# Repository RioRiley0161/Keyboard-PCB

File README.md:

# Keyboard-PCB
Custom Keyboard Design

A new project for a custom keyboard design all the way down to the PCB.
We will be making a keyboard with only 41 keys *full sized keyboards are 104 keys
Please feel free to have a look at the files and use them for your own project if need be.
Thanks

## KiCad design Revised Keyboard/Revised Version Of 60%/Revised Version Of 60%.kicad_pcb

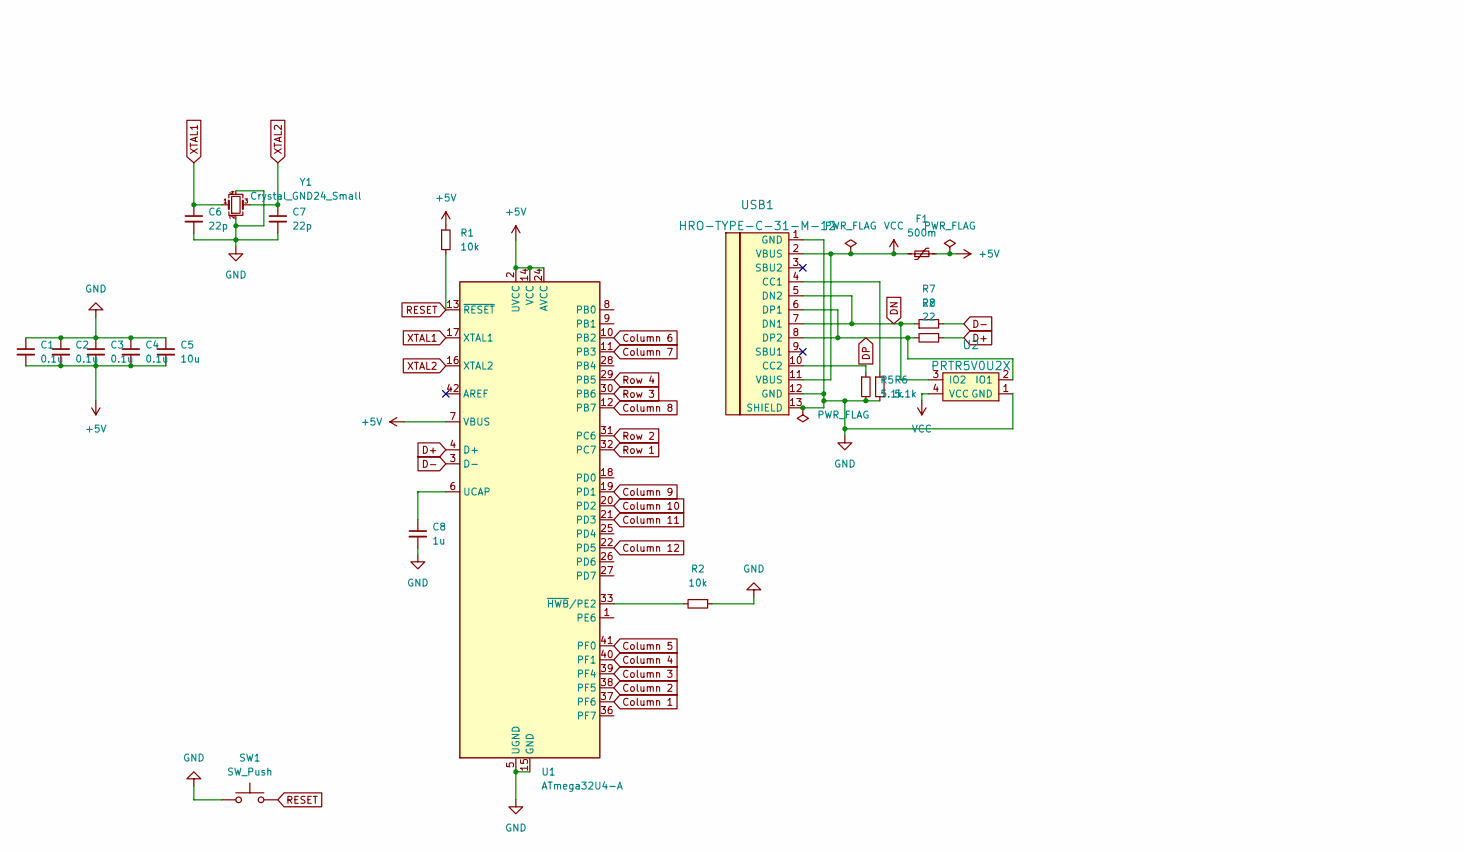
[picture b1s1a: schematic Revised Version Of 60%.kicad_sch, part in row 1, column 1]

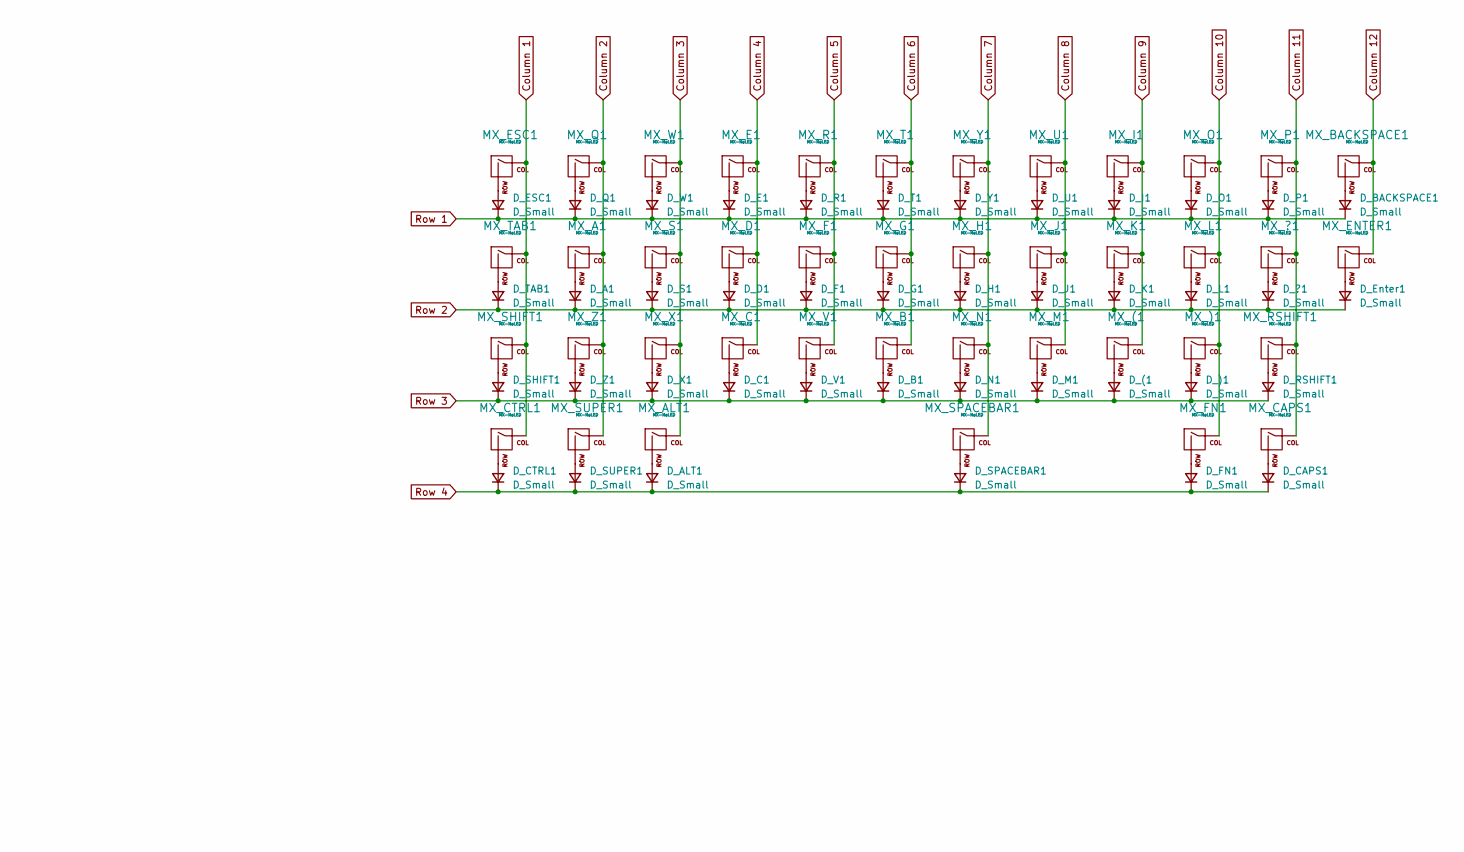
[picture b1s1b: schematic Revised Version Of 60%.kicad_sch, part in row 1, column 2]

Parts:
C1, C2, C3, C4: 0.1u; C_0805_2012Metric_Pad1.18x1.45mm_HandSolder
C5: 10u; C_0805_2012Metric_Pad1.18x1.45mm_HandSolder
C6, C7: 22p; C_0805_2012Metric_Pad1.18x1.45mm_HandSolder
C8: 1u; C_0805_2012Metric
D_(1: D_Small; D_SOD-123
D_)1: D_Small; D_SOD-123
D_?1: D_Small; D_SOD-123
D_A1: D_Small; D_SOD-123
D_ALT1: D_Small; D_SOD-123
D_B1: D_Small; D_SOD-123
D_BACKSPACE1: D_Small; D_SOD-123
D_C1: D_Small; D_SOD-123
D_CAPS1: D_Small; D_SOD-123
D_CTRL1: D_Small; D_SOD-123
D_D1: D_Small; D_SOD-123
D_E1: D_Small; D_SOD-123
D_ESC1: D_Small; D_SOD-123
D_Enter1: D_Small; D_SOD-123
D_F1: D_Small; D_SOD-123
D_FN1: D_Small; D_SOD-123
D_G1: D_Small; D_SOD-123
D_H1: D_Small; D_SOD-123
D_I1: D_Small; D_SOD-123
D_J1: D_Small; D_SOD-123
D_K1: D_Small; D_SOD-123
D_L1: D_Small; D_SOD-123
D_M1: D_Small; D_SOD-123
D_N1: D_Small; D_SOD-123
D_O1: D_Small; D_SOD-123
D_P1: D_Small; D_SOD-123
D_Q1: D_Small; D_SOD-123
D_R1: D_Small; D_SOD-123
D_RSHIFT1: D_Small; D_SOD-123
D_S1: D_Small; D_SOD-123
D_SHIFT1: D_Small; D_SOD-123
D_SPACEBAR1: D_Small; D_SOD-123
D_SUPER1: D_Small; D_SOD-123
D_T1: D_Small; D_SOD-123
D_TAB1: D_Small; D_SOD-123
D_U1: D_Small; D_SOD-123
D_V1: D_Small; D_SOD-123
D_W1: D_Small; D_SOD-123
D_X1: D_Small; D_SOD-123
D_Y1: D_Small; D_SOD-123
D_Z1: D_Small; D_SOD-123
F1: 500m; Fuse_1206_3216Metric_Pad1.42x1.75mm_HandSolder
MX_(1: MX-NoLED; MX-1U-NoLED
MX_)1: MX-NoLED; MX-1U-NoLED
MX_?1: MX-NoLED; MX-1U-NoLED
MX_A1: MX-NoLED; MX-1U-NoLED
MX_ALT1: MX-NoLED; MX-1.25U-NoLED
MX_B1: MX-NoLED; MX-1U-NoLED
MX_BACKSPACE1: MX-NoLED; MX-1.75U-NoLED
MX_C1: MX-NoLED; MX-1U-NoLED
MX_CAPS1: MX-NoLED; MX-1.25U-NoLED
MX_CTRL1: MX-NoLED; MX-1.25U-NoLED
MX_D1: MX-NoLED; MX-1U-NoLED
MX_E1: MX-NoLED; MX-1U-NoLED
MX_ENTER1: MX-NoLED; MX-1.5U-NoLED
MX_ESC1: MX-NoLED; MX-1U-NoLED
MX_F1: MX-NoLED; MX-1U-NoLED
MX_FN1: MX-NoLED; MX-1.25U-NoLED
MX_G1: MX-NoLED; MX-1U-NoLED
MX_H1: MX-NoLED; MX-1U-NoLED
MX_I1: MX-NoLED; MX-1U-NoLED
MX_J1: MX-NoLED; MX-1U-NoLED
MX_K1: MX-NoLED; MX-1U-NoLED
MX_L1: MX-NoLED; MX-1U-NoLED
MX_M1: MX-NoLED; MX-1U-NoLED
MX_N1: MX-NoLED; MX-1U-NoLED
MX_O1: MX-NoLED; MX-1U-NoLED
MX_P1: MX-NoLED; MX-1U-NoLED
MX_Q1: MX-NoLED; MX-1U-NoLED
MX_R1: MX-NoLED; MX-1U-NoLED
MX_RSHIFT1: MX-NoLED; MX-2U-NoLED
MX_S1: MX-NoLED; MX-1U-NoLED
MX_SHIFT1: MX-NoLED; MX-1.75U-NoLED
MX_SPACEBAR1: MX-NoLED; MX-6.5U-NoLED
MX_SUPER1: MX-NoLED; MX-1.25U-NoLED
MX_T1: MX-NoLED; MX-1U-NoLED
MX_TAB1: MX-NoLED; MX-1.25U-NoLED
MX_U1: MX-NoLED; MX-1U-NoLED
MX_V1: MX-NoLED; MX-1U-NoLED
MX_W1: MX-NoLED; MX-1U-NoLED
MX_X1: MX-NoLED; MX-1U-NoLED
MX_Y1: MX-NoLED; MX-1U-NoLED
MX_Z1: MX-NoLED; MX-1U-NoLED
R1, R2: 10k; R_0805_2012Metric_Pad1.20x1.40mm_HandSolder
R5, R6: 5.1k; R_0805_2012Metric_Pad1.20x1.40mm_HandSolder
R7, R8: 22; R_0805_2012Metric_Pad1.20x1.40mm_HandSolder
SW1: SW_Push; SKQG-1155865
U1: ATmega32U4-A; TQFP-44_10x10mm_P0.8mm
U2: PRTR5V0U2X; SOT143B
USB1: HRO-TYPE-C-31-M-12; HRO-TYPE-C-31-M-12-HandSoldering
Y1: Crystal_GND24_Small; Crystal_SMD_3225-4Pin_3.2x2.5mm_HandSoldering

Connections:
+5V: C1.2, C2.2, C3.2, C4.2, C5.2, F1.2, R1.1, U1.2 (UVCC), U1.7 (VBUS), U1.14 (VCC), U1.24 (AVCC), U1.34 (VCC), U1.44 (AVCC)
Column 1: MX_CTRL1.1 (COL), MX_ESC1.1 (COL), MX_SHIFT1.1 (COL), MX_TAB1.1 (COL), U1.37 (PF6)
Column 2: MX_A1.1 (COL), MX_Q1.1 (COL), MX_SUPER1.1 (COL), MX_Z1.1 (COL), U1.38 (PF5)
Column 3: MX_ALT1.1 (COL), MX_S1.1 (COL), MX_W1.1 (COL), MX_X1.1 (COL), U1.39 (PF4)
Column 4: MX_C1.1 (COL), MX_D1.1 (COL), MX_E1.1 (COL), U1.40 (PF1)
Column 5: MX_F1.1 (COL), MX_R1.1 (COL), MX_V1.1 (COL), U1.41 (PF0)
Column 6: MX_B1.1 (COL), MX_G1.1 (COL), MX_T1.1 (COL), U1.10 (PB2)
Column 7: MX_H1.1 (COL), MX_N1.1 (COL), MX_SPACEBAR1.1 (COL), MX_Y1.1 (COL), U1.11 (PB3)
Column 8: MX_J1.1 (COL), MX_M1.1 (COL), MX_U1.1 (COL), U1.12 (PB7)
Column 9: MX_(1.1 (COL), MX_I1.1 (COL), MX_K1.1 (COL), U1.19 (PD1)
Column 10: MX_)1.1 (COL), MX_FN1.1 (COL), MX_L1.1 (COL), MX_O1.1 (COL), U1.20 (PD2)
Column 11: MX_?1.1 (COL), MX_CAPS1.1 (COL), MX_P1.1 (COL), MX_RSHIFT1.1 (COL), U1.21 (PD3)
Column 12: MX_BACKSPACE1.1 (COL), MX_ENTER1.1 (COL), U1.22 (PD5)
D+: R8.1, U1.4 (D+)
D-: R7.2, U1.3 (D-)
DN: R7.1, U2.3 (IO2), USB1.5 (DN2), USB1.7 (DN1)
DP: R8.2, U2.2 (IO1), USB1.6 (DP1), USB1.8 (DP2)
GND: C1.1, C2.1, C3.1, C4.1, C5.1, C6.2, C7.2, C8.2, R2.1, R5.2, R6.2, SW1.1, U1.5 (UGND), U1.15 (GND), U1.23 (GND), U1.35 (GND), U1.43 (GND), U2.1 (GND), USB1.1 (GND), USB1.12 (GND), USB1.13 (SHIELD), Y1.2, Y1.4
unnamed: C8.1, U1.6 (UCAP)
unnamed: D_(1.2 (A), MX_(1.2 (ROW)
unnamed: D_)1.2 (A), MX_)1.2 (ROW)
unnamed: D_?1.2 (A), MX_?1.2 (ROW)
unnamed: D_A1.2 (A), MX_A1.2 (ROW)
unnamed: D_ALT1.2 (A), MX_ALT1.2 (ROW)
unnamed: D_B1.2 (A), MX_B1.2 (ROW)
unnamed: D_BACKSPACE1.2 (A), MX_BACKSPACE1.2 (ROW)
unnamed: D_C1.2 (A), MX_C1.2 (ROW)
unnamed: D_CAPS1.2 (A), MX_CAPS1.2 (ROW)
unnamed: D_CTRL1.2 (A), MX_CTRL1.2 (ROW)
unnamed: D_D1.2 (A), MX_D1.2 (ROW)
unnamed: D_E1.2 (A), MX_E1.2 (ROW)
unnamed: D_ESC1.2 (A), MX_ESC1.2 (ROW)
unnamed: D_Enter1.2 (A), MX_ENTER1.2 (ROW)
unnamed: D_F1.2 (A), MX_F1.2 (ROW)
unnamed: D_FN1.2 (A), MX_FN1.2 (ROW)
unnamed: D_G1.2 (A), MX_G1.2 (ROW)
unnamed: D_H1.2 (A), MX_H1.2 (ROW)
unnamed: D_I1.2 (A), MX_I1.2 (ROW)
unnamed: D_J1.2 (A), MX_J1.2 (ROW)
unnamed: D_K1.2 (A), MX_K1.2 (ROW)
unnamed: D_L1.2 (A), MX_L1.2 (ROW)
unnamed: D_M1.2 (A), MX_M1.2 (ROW)
unnamed: D_N1.2 (A), MX_N1.2 (ROW)
unnamed: D_O1.2 (A), MX_O1.2 (ROW)
unnamed: D_P1.2 (A), MX_P1.2 (ROW)
unnamed: D_Q1.2 (A), MX_Q1.2 (ROW)
unnamed: D_R1.2 (A), MX_R1.2 (ROW)
unnamed: D_RSHIFT1.2 (A), MX_RSHIFT1.2 (ROW)
unnamed: D_S1.2 (A), MX_S1.2 (ROW)
unnamed: D_SHIFT1.2 (A), MX_SHIFT1.2 (ROW)
unnamed: D_SPACEBAR1.2 (A), MX_SPACEBAR1.2 (ROW)
unnamed: D_SUPER1.2 (A), MX_SUPER1.2 (ROW)
unnamed: D_T1.2 (A), MX_T1.2 (ROW)
unnamed: D_TAB1.2 (A), MX_TAB1.2 (ROW)
unnamed: D_U1.2 (A), MX_U1.2 (ROW)
unnamed: D_V1.2 (A), MX_V1.2 (ROW)
unnamed: D_W1.2 (A), MX_W1.2 (ROW)
unnamed: D_X1.2 (A), MX_X1.2 (ROW)
unnamed: D_Y1.2 (A), MX_Y1.2 (ROW)
unnamed: D_Z1.2 (A), MX_Z1.2 (ROW)
unnamed: R2.2, U1.33 (~HWB/PE2)
unnamed: R5.1, USB1.10 (CC2)
unnamed: R6.1, USB1.4 (CC1)
RESET: R1.2, SW1.2, U1.13 (~RESET)
Row 1: D_BACKSPACE1.1 (K), D_E1.1 (K), D_ESC1.1 (K), D_I1.1 (K), D_O1.1 (K), D_P1.1 (K), D_Q1.1 (K), D_R1.1 (K), D_T1.1 (K), D_U1.1 (K), D_W1.1 (K), D_Y1.1 (K), U1.32 (PC7)
Row 2: D_?1.1 (K), D_A1.1 (K), D_D1.1 (K), D_Enter1.1 (K), D_F1.1 (K), D_G1.1 (K), D_H1.1 (K), D_J1.1 (K), D_K1.1 (K), D_L1.1 (K), D_S1.1 (K), D_TAB1.1 (K), U1.31 (PC6)
Row 3: D_(1.1 (K), D_)1.1 (K), D_B1.1 (K), D_C1.1 (K), D_M1.1 (K), D_N1.1 (K), D_RSHIFT1.1 (K), D_SHIFT1.1 (K), D_V1.1 (K), D_X1.1 (K), D_Z1.1 (K), U1.30 (PB6)
Row 4: D_ALT1.1 (K), D_CAPS1.1 (K), D_CTRL1.1 (K), D_FN1.1 (K), D_SPACEBAR1.1 (K), D_SUPER1.1 (K), U1.29 (PB5)
VCC: F1.1, U2.4 (VCC), USB1.2 (VBUS), USB1.11 (VBUS)
XTAL1: C6.1, U1.17 (XTAL1), Y1.1
XTAL2: C7.1, U1.16 (XTAL2), Y1.3

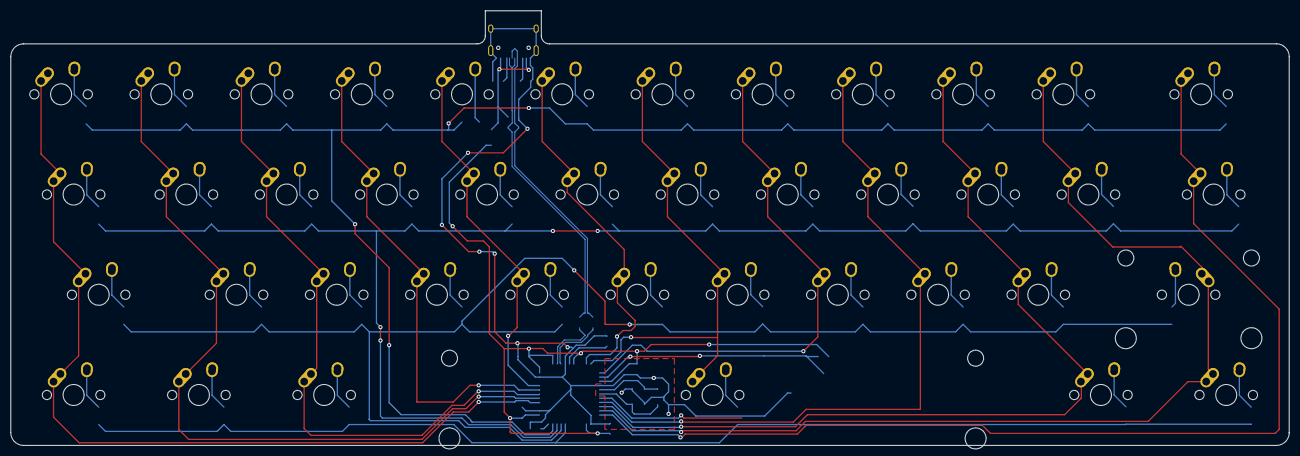
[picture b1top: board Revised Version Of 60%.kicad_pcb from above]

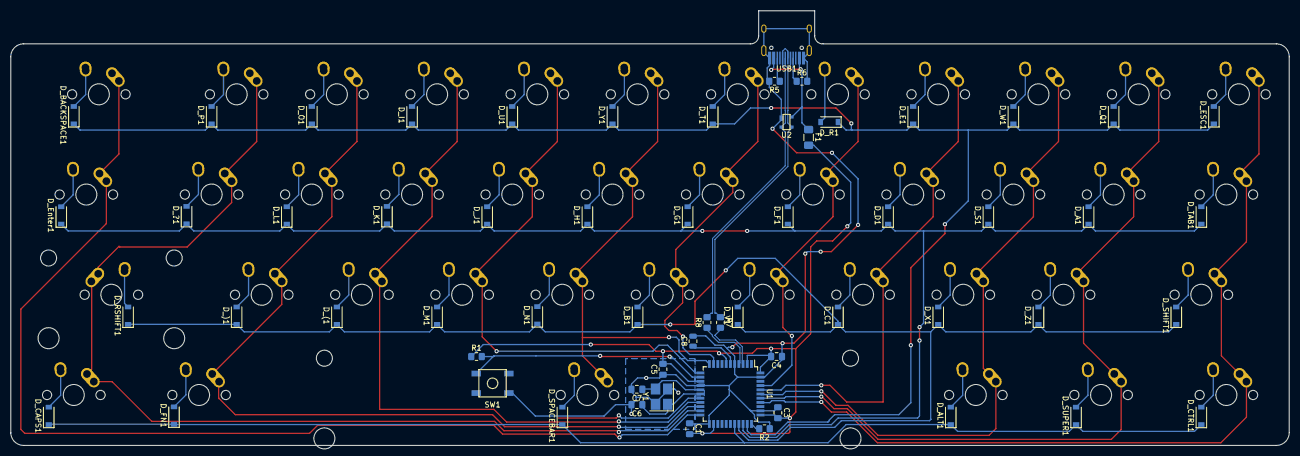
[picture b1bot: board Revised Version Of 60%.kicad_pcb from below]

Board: 2 copper layers, 243.0 x 82.6 mm, 101 parts (61 on the bottom side), 71 nets.

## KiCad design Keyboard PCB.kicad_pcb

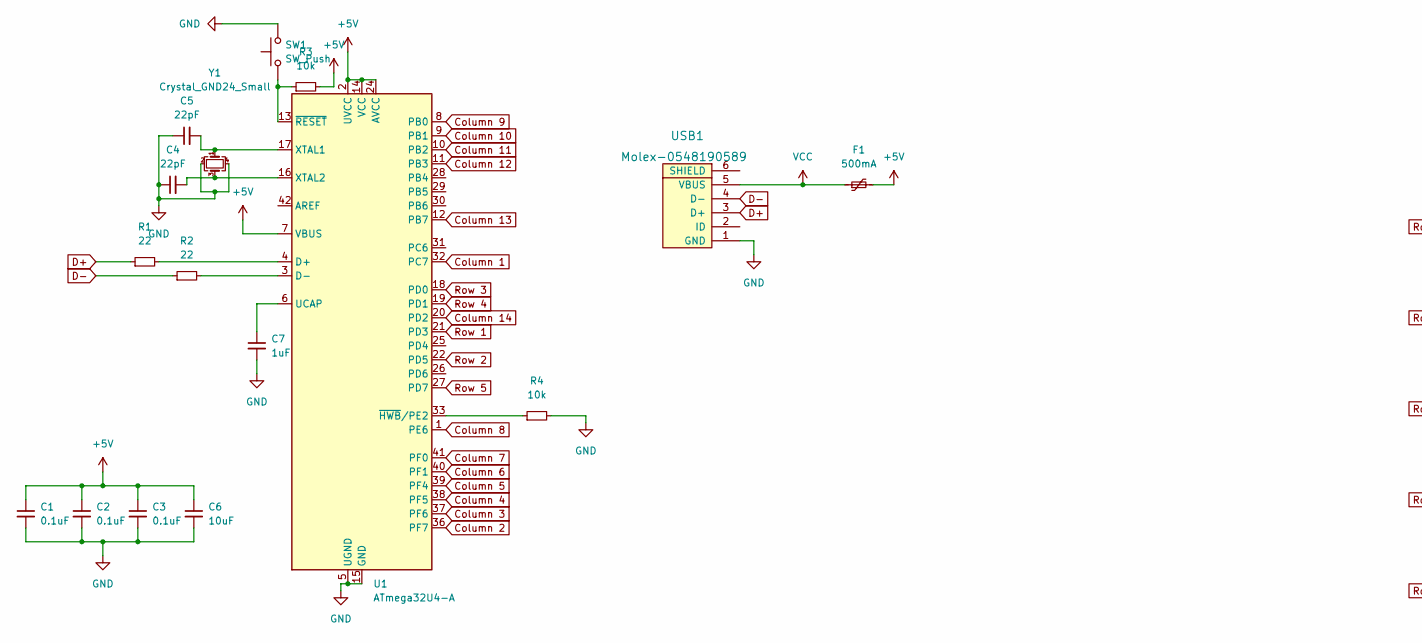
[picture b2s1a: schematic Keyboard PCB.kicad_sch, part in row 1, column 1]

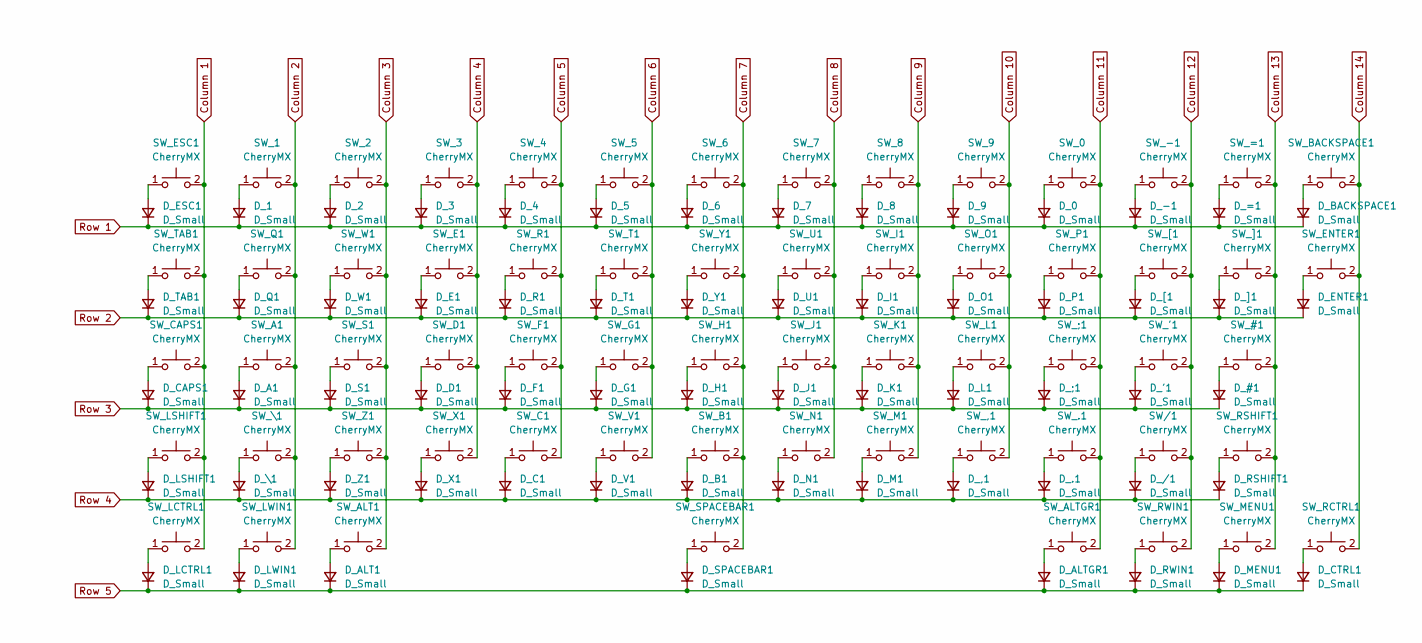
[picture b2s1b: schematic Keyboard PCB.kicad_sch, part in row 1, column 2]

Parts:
C1, C2, C3: 0.1uF; C_0805_2012Metric
C4, C5: 22pF; C_0805_2012Metric
C6: 10uF; C_0805_2012Metric
C7: 1uF; C_0805_2012Metric
D_0, D_1, D_2, D_3, D_4, D_5, D_6, D_7, D_8, D_9, D_.1: D_Small; D_SOD-123
D_#1: D_Small; D_SOD-123
D_'1: D_Small; D_SOD-123
D_,1: D_Small; D_SOD-123
D_-1: D_Small; D_SOD-123
D_/1: D_Small; D_SOD-123
D_;1: D_Small; D_SOD-123
D_=1: D_Small; D_SOD-123
D_A1: D_Small; D_SOD-123
D_ALT1: D_Small; D_SOD-123
D_ALTGR1: D_Small; D_SOD-123
D_B1: D_Small; D_SOD-123
D_BACKSPACE1: D_Small; D_SOD-123
D_C1: D_Small; D_SOD-123
D_CAPS1: D_Small; D_SOD-123
D_CTRL1: D_Small; D_SOD-123
D_D1: D_Small; D_SOD-123
D_E1: D_Small; D_SOD-123
D_ENTER1: D_Small; D_SOD-123
D_ESC1: D_Small; D_SOD-123
D_F1: D_Small; D_SOD-123
D_G1: D_Small; D_SOD-123
D_H1: D_Small; D_SOD-123
D_I1: D_Small; D_SOD-123
D_J1: D_Small; D_SOD-123
D_K1: D_Small; D_SOD-123
D_L1: D_Small; D_SOD-123
D_LCTRL1: D_Small; D_SOD-123
D_LSHIFT1: D_Small; D_SOD-123
D_LWIN1: D_Small; D_SOD-123
D_M1: D_Small; D_SOD-123
D_MENU1: D_Small; D_SOD-123
D_N1: D_Small; D_SOD-123
D_O1: D_Small; D_SOD-123
D_P1: D_Small; D_SOD-123
D_Q1: D_Small; D_SOD-123
D_R1: D_Small; D_SOD-123
D_RSHIFT1: D_Small; D_SOD-123
D_RWIN1: D_Small; D_SOD-123
D_S1: D_Small; D_SOD-123
D_SPACEBAR1: D_Small; D_SOD-123
D_T1: D_Small; D_SOD-123
D_TAB1: D_Small; D_SOD-123
D_U1: D_Small; D_SOD-123
D_V1: D_Small; D_SOD-123
D_W1: D_Small; D_SOD-123
D_X1: D_Small; D_SOD-123
D_Y1: D_Small; D_SOD-123
D_Z1: D_Small; D_SOD-123
D_[1: D_Small; D_SOD-123
D_\1: D_Small; D_SOD-123
D_]1: D_Small; D_SOD-123
F1: 500mA; Fuse_1206_3216Metric
R1, R2: 22; R_0805_2012Metric
R3, R4: 10k; R_0805_2012Metric
SW1: SW_Push; SKQG-1155865
SW/1: CherryMX; MXOnly-1U-NoLED
SW_0, SW_1, SW_2, SW_3, SW_4, SW_5, SW_6, SW_7, SW_8, SW_9, SW_.1: CherryMX; MXOnly-1U-NoLED
SW_#1: CherryMX; MXOnly-1U-NoLED
SW_'1: CherryMX; MXOnly-1U-NoLED
SW_,1: CherryMX; MXOnly-1U-NoLED
SW_-1: CherryMX; MXOnly-1U-NoLED
SW_;1: CherryMX; MXOnly-1U-NoLED
SW_=1: CherryMX; MXOnly-1U-NoLED
SW_A1: CherryMX; MXOnly-1U-NoLED
SW_ALT1: CherryMX; MXOnly-1.25U-NoLED
SW_ALTGR1: CherryMX; MXOnly-1.25U-NoLED
SW_B1: CherryMX; MXOnly-1U-NoLED
SW_BACKSPACE1: CherryMX; MXOnly-2U-NoLED
SW_C1: CherryMX; MXOnly-1U-NoLED
SW_CAPS1: CherryMX; MXOnly-1.75U-NoLED
SW_D1: CherryMX; MXOnly-1U-NoLED
SW_E1: CherryMX; MXOnly-1U-NoLED
SW_ENTER1: CherryMX; MXOnly-ISO
SW_ESC1: CherryMX; MXOnly-1U-NoLED
SW_F1: CherryMX; MXOnly-1U-NoLED
SW_G1: CherryMX; MXOnly-1U-NoLED
SW_H1: CherryMX; MXOnly-1U-NoLED
SW_I1: CherryMX; MXOnly-1U-NoLED
SW_J1: CherryMX; MXOnly-1U-NoLED
SW_K1: CherryMX; MXOnly-1U-NoLED
SW_L1: CherryMX; MXOnly-1U-NoLED
SW_LCTRL1: CherryMX; MXOnly-1.25U-NoLED
SW_LSHIFT1: CherryMX; MXOnly-1.25U-NoLED
SW_LWIN1: CherryMX; MXOnly-1.25U-NoLED
SW_M1: CherryMX; MXOnly-1U-NoLED
SW_MENU1: CherryMX; MXOnly-1.25U-NoLED
SW_N1: CherryMX; MXOnly-1U-NoLED
SW_O1: CherryMX; MXOnly-1U-NoLED
SW_P1: CherryMX; MXOnly-1U-NoLED
SW_Q1: CherryMX; MXOnly-1U-NoLED
SW_R1: CherryMX; MXOnly-1U-NoLED
SW_RCTRL1: CherryMX; MXOnly-1.25U-NoLED
SW_RSHIFT1: CherryMX; MXOnly-2.75U-NoLED
SW_RWIN1: CherryMX; MXOnly-1.25U-NoLED
SW_S1: CherryMX; MXOnly-1U-NoLED
SW_SPACEBAR1: CherryMX; MXOnly-6.25U-NoLED
SW_T1: CherryMX; MXOnly-1U-NoLED
SW_TAB1: CherryMX; MXOnly-1.5U-NoLED
SW_U1: CherryMX; MXOnly-1U-NoLED
SW_V1: CherryMX; MXOnly-1U-NoLED
SW_W1: CherryMX; MXOnly-1U-NoLED
SW_X1: CherryMX; MXOnly-1U-NoLED
SW_Y1: CherryMX; MXOnly-1U-NoLED
SW_Z1: CherryMX; MXOnly-1U-NoLED
SW_[1: CherryMX; MXOnly-1U-NoLED
SW_\1: CherryMX; MXOnly-1U-NoLED
SW_]1: CherryMX; MXOnly-1U-NoLED
U1: ATmega32U4-A; TQFP-44_10x10mm_P0.8mm
USB1: Molex-0548190589
Y1: Crystal_GND24_Small; Crystal_SMD_3225-4Pin_3.2x2.5mm_HandSoldering

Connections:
+5V: C1.1, C2.1, C3.1, C6.1, F1.2, R3.2, U1.2 (UVCC), U1.7 (VBUS), U1.14 (VCC), U1.24 (AVCC), U1.34 (VCC), U1.44 (AVCC)
Column 1: SW_CAPS1.2, SW_ESC1.2, SW_LCTRL1.2, SW_LSHIFT1.2, SW_TAB1.2, U1.32 (PC7)
Column 2: SW_1.2, SW_A1.2, SW_LWIN1.2, SW_Q1.2, SW_\1.2, U1.36 (PF7)
Column 3: SW_2.2, SW_ALT1.2, SW_S1.2, SW_W1.2, SW_Z1.2, U1.37 (PF6)
Column 4: SW_3.2, SW_D1.2, SW_E1.2, SW_X1.2, U1.38 (PF5)
Column 5: SW_4.2, SW_C1.2, SW_F1.2, SW_R1.2, U1.39 (PF4)
Column 6: SW_5.2, SW_G1.2, SW_T1.2, SW_V1.2, U1.40 (PF1)
Column 7: SW_6.2, SW_B1.2, SW_H1.2, SW_SPACEBAR1.2, SW_Y1.2, U1.41 (PF0)
Column 8: SW_7.2, SW_J1.2, SW_N1.2, SW_U1.2, U1.1 (PE6)
Column 9: SW_8.2, SW_I1.2, SW_K1.2, SW_M1.2, U1.8 (PB0)
Column 10: SW_9.2, SW_,1.2, SW_L1.2, SW_O1.2, U1.9 (PB1)
Column 11: SW_0.2, SW_.1.2, SW_;1.2, SW_ALTGR1.2, SW_P1.2, U1.10 (PB2)
Column 12: SW/1.2, SW_'1.2, SW_-1.2, SW_RWIN1.2, SW_[1.2, U1.11 (PB3)
Column 13: SW_#1.2, SW_=1.2, SW_MENU1.2, SW_RSHIFT1.2, SW_]1.2, U1.12 (PB7)
Column 14: SW_BACKSPACE1.2, SW_ENTER1.2, SW_RCTRL1.2, U1.20 (PD2)
D+: R1.1, USB1.3 (D+)
D-: R2.1, USB1.4 (D-)
GND: C1.2, C2.2, C3.2, C4.1, C5.1, C6.2, C7.2, R4.2, SW1.2, U1.5 (UGND), U1.15 (GND), U1.23 (GND), U1.35 (GND), U1.43 (GND), USB1.1 (GND), Y1.2, Y1.4
unnamed: C4.2, U1.16 (XTAL2), Y1.3
unnamed: C5.2, U1.17 (XTAL1), Y1.1
unnamed: C7.1, U1.6 (UCAP)
unnamed: D_0.2 (A), SW_0.1
unnamed: D_1.2 (A), SW_1.1
unnamed: D_2.2 (A), SW_2.1
unnamed: D_3.2 (A), SW_3.1
unnamed: D_4.2 (A), SW_4.1
unnamed: D_5.2 (A), SW_5.1
unnamed: D_6.2 (A), SW_6.1
unnamed: D_7.2 (A), SW_7.1
unnamed: D_8.2 (A), SW_8.1
unnamed: D_9.2 (A), SW_9.1
unnamed: D_#1.2 (A), SW_#1.1
unnamed: D_'1.2 (A), SW_'1.1
unnamed: D_,1.2 (A), SW_,1.1
unnamed: D_-1.2 (A), SW_-1.1
unnamed: D_.1.2 (A), SW_.1.1
unnamed: D_/1.2 (A), SW/1.1
unnamed: D_;1.2 (A), SW_;1.1
unnamed: D_=1.2 (A), SW_=1.1
unnamed: D_A1.2 (A), SW_A1.1
unnamed: D_ALT1.2 (A), SW_ALT1.1
unnamed: D_ALTGR1.2 (A), SW_ALTGR1.1
unnamed: D_B1.2 (A), SW_B1.1
unnamed: D_BACKSPACE1.2 (A), SW_BACKSPACE1.1
unnamed: D_C1.2 (A), SW_C1.1
unnamed: D_CAPS1.2 (A), SW_CAPS1.1
unnamed: D_CTRL1.2 (A), SW_RCTRL1.1
unnamed: D_D1.2 (A), SW_D1.1
unnamed: D_E1.2 (A), SW_E1.1
unnamed: D_ENTER1.2 (A), SW_ENTER1.1
unnamed: D_ESC1.2 (A), SW_ESC1.1
unnamed: D_F1.2 (A), SW_F1.1
unnamed: D_G1.2 (A), SW_G1.1
unnamed: D_H1.2 (A), SW_H1.1
unnamed: D_I1.2 (A), SW_I1.1
unnamed: D_J1.2 (A), SW_J1.1
unnamed: D_K1.2 (A), SW_K1.1
unnamed: D_L1.2 (A), SW_L1.1
unnamed: D_LCTRL1.2 (A), SW_LCTRL1.1
unnamed: D_LSHIFT1.2 (A), SW_LSHIFT1.1
unnamed: D_LWIN1.2 (A), SW_LWIN1.1
unnamed: D_M1.2 (A), SW_M1.1
unnamed: D_MENU1.2 (A), SW_MENU1.1
unnamed: D_N1.2 (A), SW_N1.1
unnamed: D_O1.2 (A), SW_O1.1
unnamed: D_P1.2 (A), SW_P1.1
unnamed: D_Q1.2 (A), SW_Q1.1
unnamed: D_R1.2 (A), SW_R1.1
unnamed: D_RSHIFT1.2 (A), SW_RSHIFT1.1
unnamed: D_RWIN1.2 (A), SW_RWIN1.1
unnamed: D_S1.2 (A), SW_S1.1
unnamed: D_SPACEBAR1.2 (A), SW_SPACEBAR1.1
unnamed: D_T1.2 (A), SW_T1.1
unnamed: D_TAB1.2 (A), SW_TAB1.1
unnamed: D_U1.2 (A), SW_U1.1
unnamed: D_V1.2 (A), SW_V1.1
unnamed: D_W1.2 (A), SW_W1.1
unnamed: D_X1.2 (A), SW_X1.1
unnamed: D_Y1.2 (A), SW_Y1.1
unnamed: D_Z1.2 (A), SW_Z1.1
unnamed: D_[1.2 (A), SW_[1.1
unnamed: D_\1.2 (A), SW_\1.1
unnamed: D_]1.2 (A), SW_]1.1
unnamed: R1.2, U1.4 (D+)
unnamed: R2.2, U1.3 (D-)
unnamed: R3.1, SW1.1, U1.13 (~RESET)
unnamed: R4.1, U1.33 (~HWB/PE2)
Row 1: D_0.1 (K), D_1.1 (K), D_2.1 (K), D_3.1 (K), D_4.1 (K), D_5.1 (K), D_6.1 (K), D_7.1 (K), D_8.1 (K), D_9.1 (K), D_-1.1 (K), D_=1.1 (K), D_BACKSPACE1.1 (K), D_ESC1.1 (K), U1.21 (PD3)
Row 2: D_E1.1 (K), D_ENTER1.1 (K), D_I1.1 (K), D_O1.1 (K), D_P1.1 (K), D_Q1.1 (K), D_R1.1 (K), D_T1.1 (K), D_TAB1.1 (K), D_U1.1 (K), D_W1.1 (K), D_Y1.1 (K), D_[1.1 (K), D_]1.1 (K), U1.22 (PD5)
Row 3: D_#1.1 (K), D_'1.1 (K), D_;1.1 (K), D_A1.1 (K), D_CAPS1.1 (K), D_D1.1 (K), D_F1.1 (K), D_G1.1 (K), D_H1.1 (K), D_J1.1 (K), D_K1.1 (K), D_L1.1 (K), D_S1.1 (K), U1.18 (PD0)
Row 4: D_,1.1 (K), D_.1.1 (K), D_/1.1 (K), D_B1.1 (K), D_C1.1 (K), D_LSHIFT1.1 (K), D_M1.1 (K), D_N1.1 (K), D_RSHIFT1.1 (K), D_V1.1 (K), D_X1.1 (K), D_Z1.1 (K), D_\1.1 (K), U1.19 (PD1)
Row 5: D_ALT1.1 (K), D_ALTGR1.1 (K), D_CTRL1.1 (K), D_LCTRL1.1 (K), D_LWIN1.1 (K), D_MENU1.1 (K), D_RWIN1.1 (K), D_SPACEBAR1.1 (K), U1.27 (PD7)
VCC: F1.1, USB1.5 (VBUS)

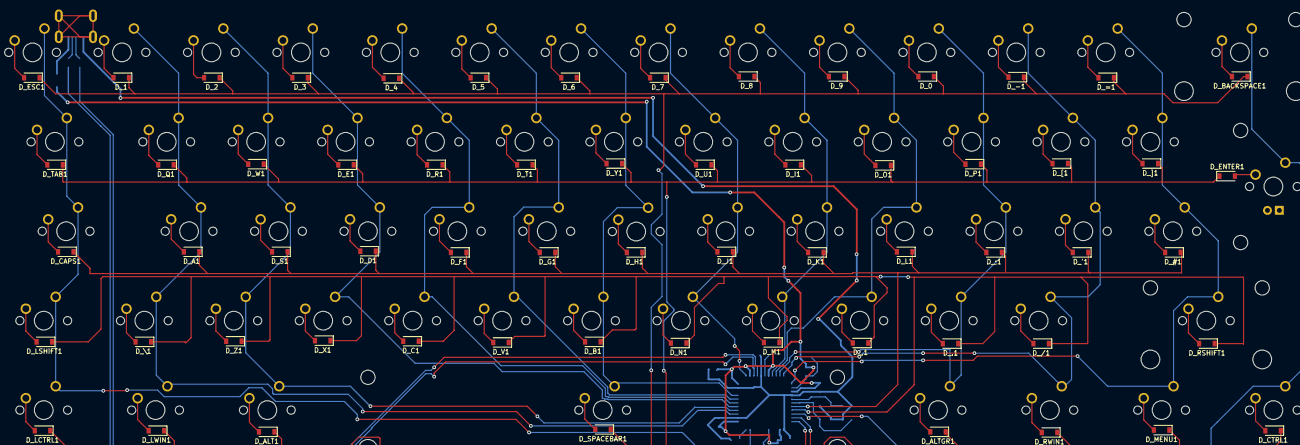
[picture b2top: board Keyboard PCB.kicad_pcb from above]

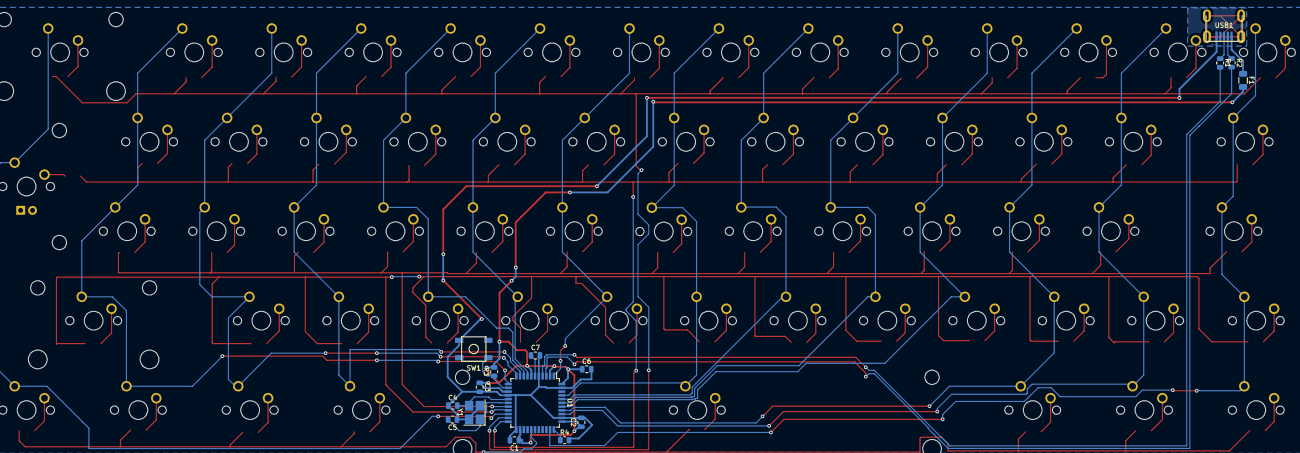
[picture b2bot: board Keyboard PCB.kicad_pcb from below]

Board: 2 copper layers, 140 parts (16 on the bottom side), 93 nets.

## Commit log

2022-01-31 Starter
    Libraries added
    New project file on KiCad started
    Keyboard Layout Added
2022-01-31 Libraries updated on KiCad
    Updated Libraries on KiCad
2022-02-02 Keyboard completed
    Keyboard is finished in all aspects.
    Their is only one problem with the footprint for the USB, but as this is just a base design which i will use to help me make my revised version i will be leaving it.
2022-02-02 Complete
    Ready for revision
2022-02-02 Revised 60%
    Revised 60% folder created, layouts are added for keyboard and numpad add on. Libraries all been added.
2022-02-03 Revised Version Updated
    Schematic completed for the base keyboard
2022-02-03 Updated PCB
2022-02-06 Update
    General Update of files
2022-02-23 Keyboard Update
    Changed to a smaller microcontroller
2022-02-28 Keyboard Nearly finished
    All components wired up on the PCB
